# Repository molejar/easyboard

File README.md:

# Rapid Development Platform

EasyBoard Nano (EBN) represent the hardware modular concept for rapid development and prototyping.
Thanks to high scalability it's covering a wide area of applications and technologies.

## EBN HW

## EBN SW

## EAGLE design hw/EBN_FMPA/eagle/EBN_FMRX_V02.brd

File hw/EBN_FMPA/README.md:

# EBN: FM Radio Shield

#### General Info

* **Base On:** RDA5807M (Single-Chip Broadcast FM Radio Tuner with RDS)
* **Output PA:** PAM8403/PAM8406 (FilterLess 3W/5W Class-D Stereo Audio Amplifier)
* **Control Pins:** Two GPIOs for Enable/Disable MUTE and SHUTDOWN
* **Main Interface:** I2C for tuning and controlling RDA5807M

### Blocking Diagram

### PinOut

#### Connection with Core Shield

| EBN-FMPA        | EBN-KL27Z4  |
| --------------- | ----------- |
| I2C-SDA         | PTB1        |
| I2C-SCL         | PTB0        |
| SHDN            | PTA1        |
| MUTE            | PTA2        |
| AIO             | PTE30       |

### Design files

 * [Schematic & PCB (Eagle 7.x)](eagle)

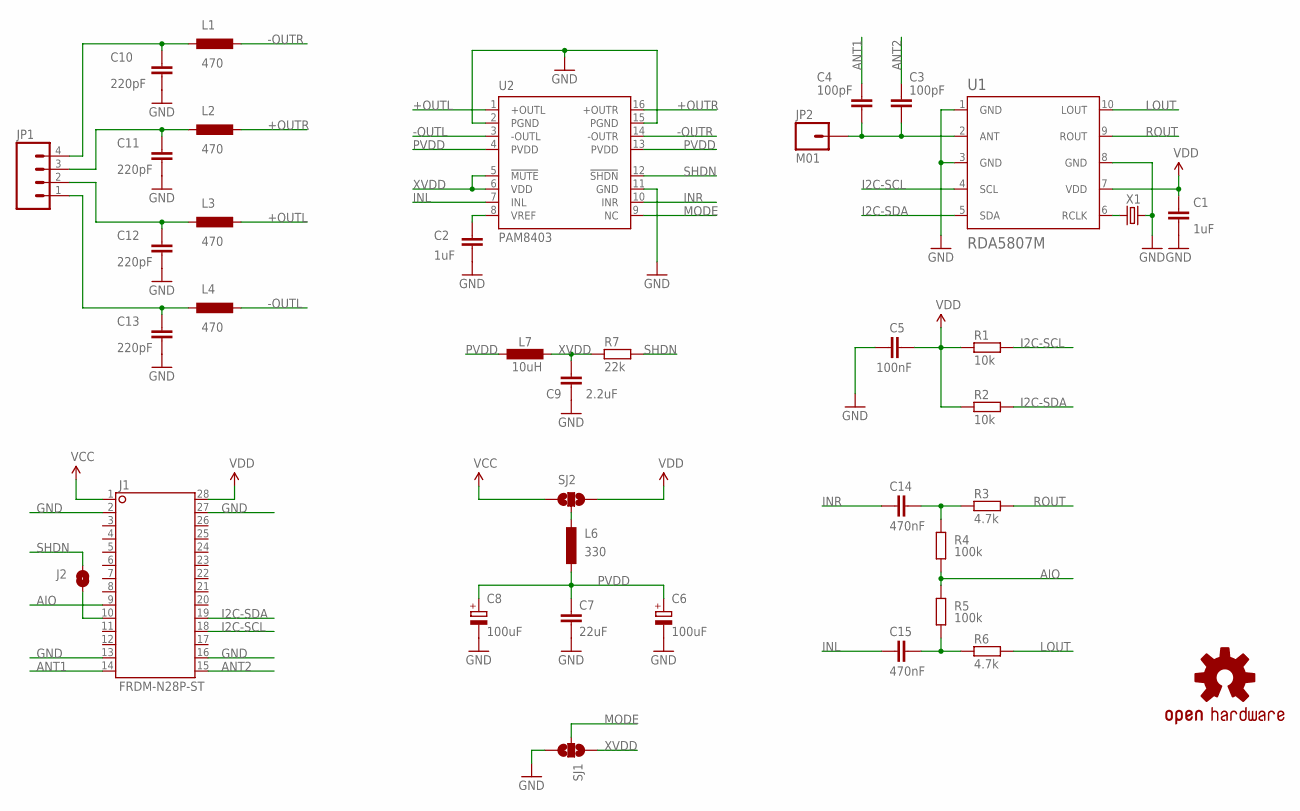
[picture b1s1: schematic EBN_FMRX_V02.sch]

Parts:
C1, C2: 1uF; C0603
C3, C4: 100pF; C0603
C5: 100nF; C0603
C6, C8: 100uF; SMC_C
C7: 22uF; C1206
C9: 2.2uF; C0603
C10, C11, C12, C13: 220pF; C0603
C14, C15: 470nF; C0603
J1: FRDM-N28P-ST; FRDM-N28P-SHIELD
J2: SJ-S; JUMPER-SMD-S1X
JP1: M04SMD_1.25MM; 1X04-1.25MM_SMD
JP2: M01; 1X01-EXTRA
L1, L2, L3, L4: 470; L0805
L6: 330; L0805
L7: 10uH; L0805
LOGO1: OSHW-LOGOS; OSHW-LOGO-S
R1, R2: 10k; R0603
R3, R6: 4.7k; R0603
R4, R5: 100k; R0603
R7: 22k; R0603
SJ1, SJ2: SJ2W-S; JUMPER-SMD-S2X
U1: RDA5807M; MSOP10
U2: PAM8403; SO16
X1: XTAL1-SMD-2P-3.2X1.5MM; SMD-2X-3215

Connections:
+OUTL: L3.2, U2.1 (+OUTL)
+OUTR: L2.2, U2.16 (+OUTR)
-OUTL: L4.2, U2.3 (-OUTL)
-OUTR: L1.2, U2.14 (-OUTR)
AIO: J1.9, R4.2, R5.2
ANT1: C4.1, J1.14
ANT2: C3.1, J1.15
GND: C1.1, C2.2, C5.2, C6.-, C7.1, C8.-, C9.1, C10.1, C11.1, C12.1, C13.1, J1.2, J1.13, J1.16, J1.27, SJ1.3, U1.1 (GND), U1.3 (GND), U1.8 (GND), U2.2 (PGND), U2.11 (GND), U2.15 (PGND), X1.2
I2C-SCL: J1.18, R1.2, U1.4 (SCL)
I2C-SDA: J1.19, R2.2, U1.5 (SDA)
INL: C15.2, U2.7 (INL)
INR: C14.2, U2.10 (INR)
LOUT: R6.2, U1.10 (LOUT)
MODE: SJ1.2, U2.9 (NC)
unnamed: C2.1, U2.8 (VREF)
unnamed: C10.2, JP1.4, L1.1
unnamed: C3.2, C4.2, JP2.P$1, U1.2 (ANT)
unnamed: C11.2, JP1.3, L2.1
unnamed: C12.2, JP1.2, L3.1
unnamed: U1.6 (RCLK), X1.1
unnamed: J1.10, J2.1
unnamed: C13.2, JP1.1, L4.1
unnamed: L6.2, SJ2.2
unnamed: C14.1, R3.1, R4.1
unnamed: C15.1, R5.1, R6.1
PVDD: C6.+, C7.2, C8.+, L6.1, L7.1, U2.4 (PVDD), U2.13 (PVDD)
ROUT: R3.2, U1.9 (ROUT)
SHDN: J2.2, R7.2, U2.12 (!SHDN)
VCC: J1.1, SJ2.1
VDD: C1.2, C5.1, J1.28, R1.1, R2.1, SJ2.3, U1.7 (VDD)
XVDD: C9.2, L7.2, R7.1, SJ1.1, U2.5 (!MUTE), U2.6 (VDD)

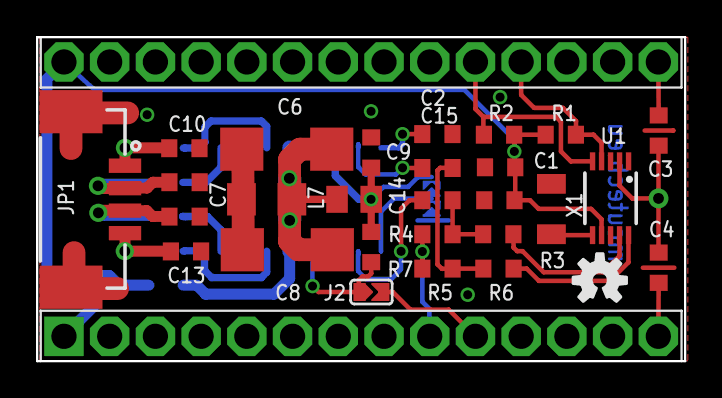
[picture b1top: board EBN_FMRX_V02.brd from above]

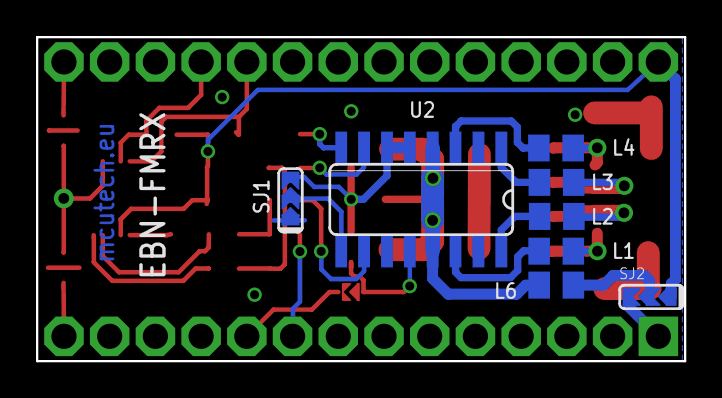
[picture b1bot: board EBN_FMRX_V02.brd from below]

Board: 2 copper layers, 36.0 x 18.0 mm, 38 parts (8 on the bottom side), 31 nets.

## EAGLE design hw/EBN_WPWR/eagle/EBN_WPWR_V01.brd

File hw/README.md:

# EasyBoard Nano HW

* [EBN_KL27Z4](EBN_KL27Z4) - KL27Z4 Core Shield
* [EBN_FMPA](EBN_FMPA) - FM Radio + 2x5W PA Shield
* [EBN_OLED](EBN_OLED) - I2C and SPI OLED Shield
* [EBN_S12D](EBN_S12D) - 12 Dimension Sensor Shield
* [EBN_WPWR](EBN_WPWR) - Wireless Power Shield
* [EBN_SBAT](EBN_SBAT) - Smart Battery Shield
* [EBN_STOR](EBN_STOR) - Storage Shield
* [EBN_GPS](EBN_GPS) - GPS + SD Card Shield
* [EBN_DUAL](EBN_DUAL) - Extendable Shield
* [EBN_PROTO](EBN_PROTO) - Prototype Shield

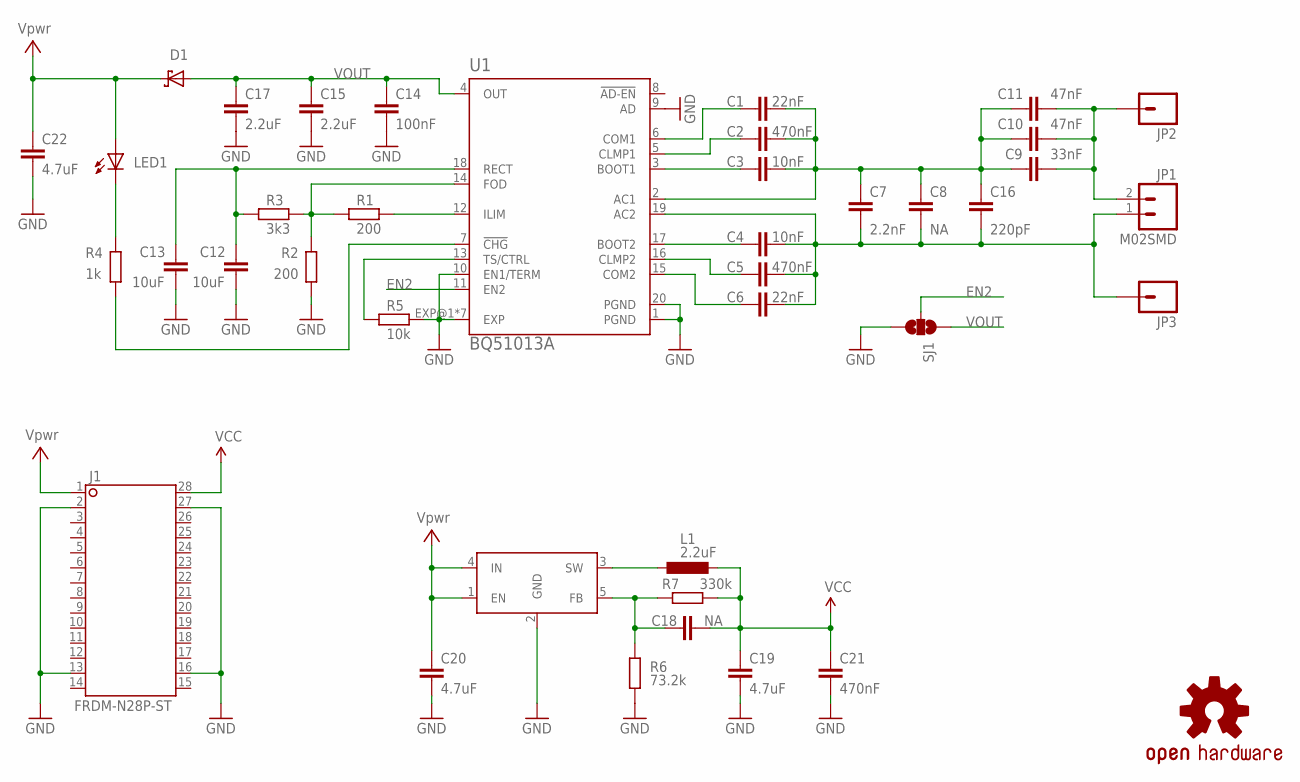
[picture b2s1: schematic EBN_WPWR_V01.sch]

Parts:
C1, C6: 22nF; C0603
C2, C5, C21: 470nF; C0603
C3, C4: 10nF; C0603
C7: 2.2nF; C0603
C8, C18: NA; C0603
C9: 33nF; C0603
C10, C11: 47nF; C0603
C12, C13: 10uF; C0805
C14: 100nF; C0603
C15, C17: 2.2uF; C0603
C16: 220pF; C0603
C19, C20, C22: 4.7uF; C0603
D1: PMEG2010BER-SHOTTKY-SOD123FL; SOD-123FL
J1: FRDM-N28P-ST; FRDM-N28P-SHIELD
JP1: M02SMD; 1X02-1.25MM_SMD
JP2, JP3: M01PTH_LONGPAD; 1X01_LONGPAD
L1: 2.2uF; LPS3015
LED1: LEDCHIPLED_0603; CHIPLED_0603
LOGO1: OSHW-LOGOS; OSHW-LOGO-S
R1, R2: 200; R0603
R3: 3k3; R0603
R4: 1k; R0603
R5: 10k; R0603
R6: 73.2k; R0603
R7: 330k; R0603
SJ1: SJ2W-S; JUMPER-SMD-S2X
U1: BQ51013A; RHL_R-VQFN-N20
U$1: MP215P; SOT23-5L

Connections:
EN2: SJ1.2, U1.11 (EN2)
GND: C12.1, C13.1, C14.1, C15.1, C17.1, C19.1, C20.1, C21.1, C22.1, J1.2, J1.13, J1.16, J1.27, R2.1, R5.2, R6.1, SJ1.3, U1.1 (PGND), U1.9 (AD), U1.10 (EN1/TERM), U1.20 (PGND), U1.EXP@1 (EXP), U1.EXP@2 (EXP), U1.EXP@3 (EXP), U1.EXP@4 (EXP), U1.EXP@5 (EXP), U1.EXP@6 (EXP), U1.EXP@7 (EXP), U$1.2 (GND)
unnamed: C3.1, U1.3 (BOOT1)
unnamed: C2.1, U1.5 (CLMP1)
unnamed: C1.1, U1.6 (COM1)
unnamed: C1.2, C2.2, C3.2, C7.2, C8.2, C9.2, C10.2, C11.2, C16.2, U1.2 (AC1)
unnamed: C4.2, C5.2, C6.2, C7.1, C8.1, C16.1, JP1.1, JP3.1, U1.19 (AC2)
unnamed: C4.1, U1.17 (BOOT2)
unnamed: C5.1, U1.16 (CLMP2)
unnamed: C6.1, U1.15 (COM2)
unnamed: C9.1, C10.1, C11.1, JP1.2, JP2.1
unnamed: LED1.C, R4.2
unnamed: R4.1, U1.7 (!CHG)
unnamed: R1.2, U1.12 (ILIM)
unnamed: R1.1, R2.2, R3.1, U1.14 (FOD)
unnamed: C12.2, C13.2, R3.2, U1.18 (RECT)
unnamed: L1.P$1 (1), U$1.3 (SW)
unnamed: C18.2, R6.2, R7.2, U$1.5 (FB)
PWR: C20.2, C22.2, D1.C, J1.1, LED1.A, U$1.1 (EN), U$1.4 (IN)
TS: R5.1, U1.13 (TS/CTRL)
VCC: C18.1, C19.2, C21.2, J1.28, L1.P$2 (2), R7.1
VOUT: C14.2, C15.2, C17.2, D1.A, SJ1.1, U1.4 (OUT)

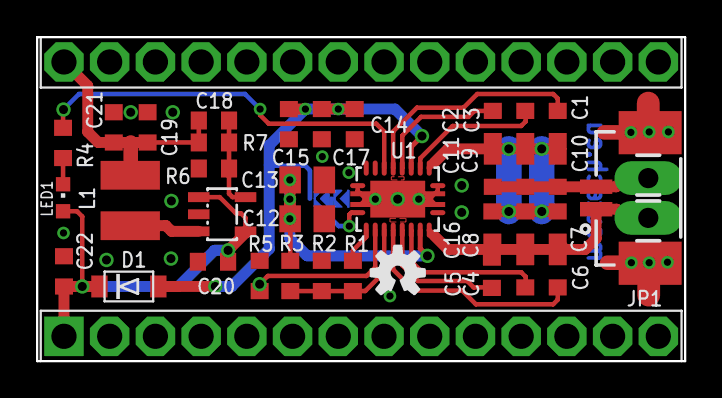
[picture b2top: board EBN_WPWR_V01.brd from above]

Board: 2 copper layers, 36.0 x 18.0 mm, 40 parts (1 on the bottom side), 22 nets.

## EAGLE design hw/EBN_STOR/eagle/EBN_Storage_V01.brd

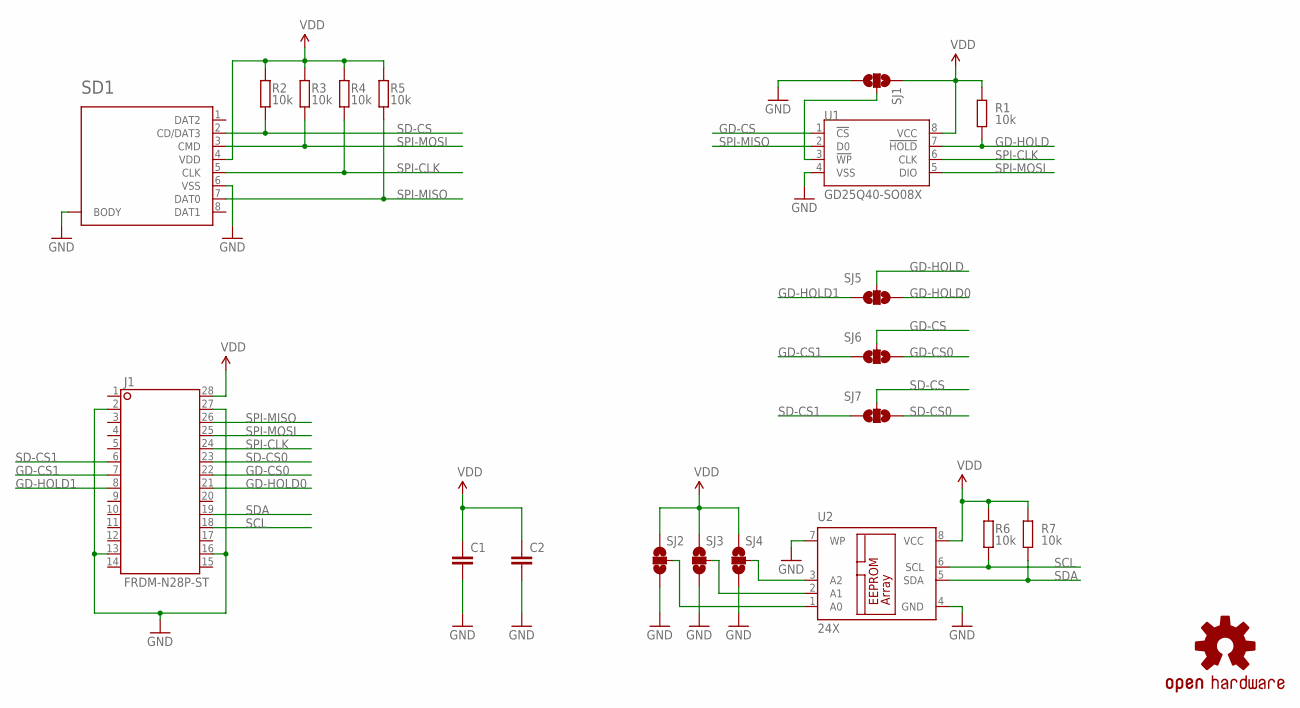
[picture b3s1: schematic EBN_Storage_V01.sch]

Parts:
C1: C-EUC0402; C0402
C2: C-EUC0603; C0603
J1: FRDM-N28P-ST; FRDM-N28P-SHIELD
LOGO1: OSHW-LOGOM; OSHW-LOGO-M
R1, R6, R7: 10k; R0603
R2, R3, R4, R5: 10k; R0402
SD1: SDCARD; MICRO-SD-01
SJ1, SJ2, SJ3, SJ4, SJ5, SJ6, SJ7: SJ2W-S; JUMPER-SMD-S2X
U1: GD25Q40-SO08X; SO08X@1
U2: 24X; SO08X

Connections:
GD-CS: SJ6.2, U1.1 (!CS)
GD-CS0: J1.22, SJ6.1
GD-CS1: J1.7, SJ6.3
GD-HOLD: R1.1, SJ5.2, U1.7 (!HOLD)
GD-HOLD0: J1.21, SJ5.1
GD-HOLD1: J1.8, SJ5.3
GND: C1.2, C2.2, J1.2, J1.13, J1.16, J1.27, SD1.6 (VSS), SD1.SHELD@0 (BODY), SD1.SHELD@1 (BODY), SJ1.1, SJ2.1, SJ3.1, SJ4.1, U1.4 (VSS), U2.4 (GND), U2.7 (WP)
unnamed: SJ4.2, U2.3 (A2)
unnamed: SJ1.2, U1.3 (!WP)
unnamed: SJ3.2, U2.2 (A1)
unnamed: SJ2.2, U2.1 (A0)
SCL: J1.18, R6.1, U2.6 (SCL)
SD-CS: R2.1, SD1.2 (CD/DAT3), SJ7.2
SD-CS0: J1.23, SJ7.1
SD-CS1: J1.6, SJ7.3
SDA: J1.19, R7.1, U2.5 (SDA)
SPI-CLK: J1.24, R4.1, SD1.5 (CLK), U1.6 (CLK)
SPI-MISO: J1.26, R5.1, SD1.7 (DAT0), U1.2 (D0)
SPI-MOSI: J1.25, R3.1, SD1.3 (CMD), U1.5 (DIO)
VDD: C1.1, C2.1, J1.28, R1.2, R2.2, R3.2, R4.2, R5.2, R6.2, R7.2, SD1.4 (VDD), SJ1.3, SJ2.3, SJ3.3, SJ4.3, U1.8 (VCC), U2.8 (VCC)

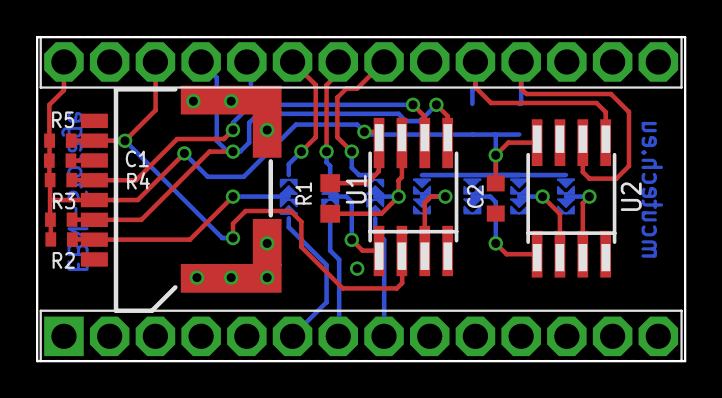
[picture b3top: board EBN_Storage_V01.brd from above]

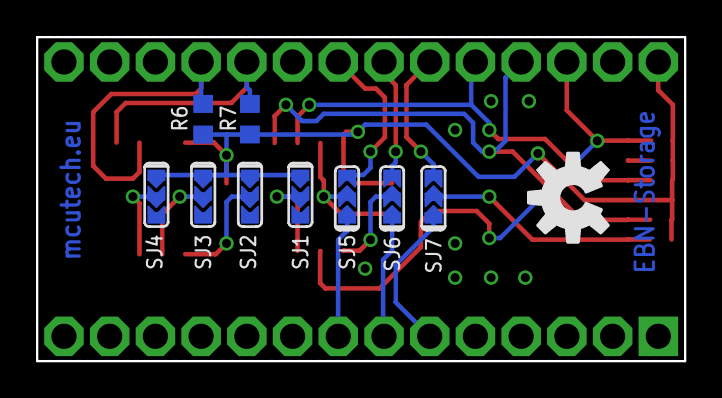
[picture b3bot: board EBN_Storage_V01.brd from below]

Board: 2 copper layers, 36.0 x 18.0 mm, 21 parts (10 on the bottom side), 20 nets.

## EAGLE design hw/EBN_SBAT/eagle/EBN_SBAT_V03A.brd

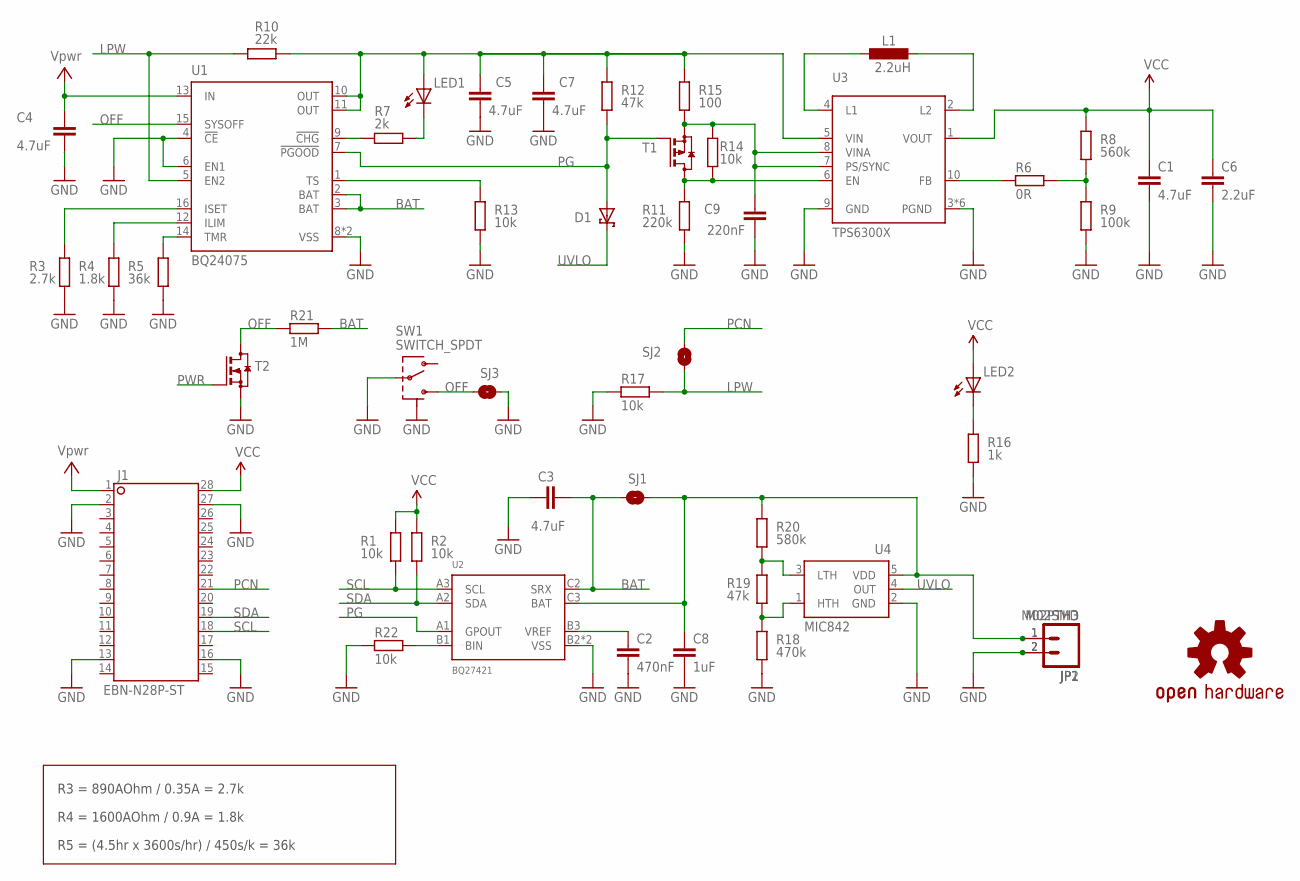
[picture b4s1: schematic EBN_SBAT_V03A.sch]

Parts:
C1, C4, C5, C7: 4.7uF; C0603
C2: 470nF; C0402
C3: 4.7uF; C0805
C6: 2.2uF; C0603
C8: 1uF; C0402
C9: 220nF; C0402
D1: -SHOTTKY-SOD323_ST; SOD323_ST
J1: EBN-N28P-ST; EBN-N28P-SHIELD
JP1: M02SMD; 1X02-1.25MM_SMD
JP2: M02PTH3; 1X02_LONGPADS
L1: 2.2uH; LPS3015
LED1, LED2: LEDCHIPLED_0603; CHIPLED_0603
LOGO1: OSHW-LOGOS; OSHW-LOGO-S
R1, R2, R13, R14, R17, R22: 10k; R0402
R3: 2.7k; R0402
R4: 1.8k; R0402
R5: 36k; R0402
R6: 0R; R0402
R7: 2k; R0402
R8: 560k; R0402
R9: 100k; R0402
R10: 22k; R0402
R11: 220k; R0402
R12, R19: 47k; R0402
R15: 100; R0402
R16: 1k; R0402
R18: 470k; R0402
R20: 580k; R0402
R21: 1M; R0402
SJ1, SJ2, SJ3: SJ-S; JUMPER-SMD-S1X
SW1: SWITCH_SPDT; SWITCH-SPST-SMD-A
T1: -PMOS-SOT323; SOT323
T2: -NMOS-SOT323; SOT323
U1: BQ24075; QFN16-3X3MM
U2: BQ27421; XBGA9
U3: TPS6300X; QFN-10_PAD
U4: MIC842; SC70

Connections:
BAT: C3.1, R21.1, SJ1.2, U1.2 (BAT), U1.3 (BAT), U2.C2 (SRX)
BATX: C8.2, JP1.1, JP2.1, R20.1, SJ1.1, U2.C3 (BAT), U4.5 (VDD)
GND: C1.2, C2.1, C3.2, C4.2, C5.2, C6.2, C7.2, C8.1, C9.2, J1.2, J1.13, J1.16, J1.27, JP1.2, JP2.2, R3.1, R4.1, R5.1, R9.1, R11.1, R13.1, R16.1, R17.2, R18.1, R22.2, SJ3.2, SW1.2, SW1.GND1 (SH), SW1.GND2 (SH), SW1.GND3 (SH), SW1.GND4 (SH), T2.2 (S), U1.4 (!CE), U1.6 (EN1), U1.8 (VSS), U1.EXT (VSS), U2.B2 (VSS), U2.C1 (VSS), U3.3 (PGND), U3.9 (GND), U3.11 (PGND), U3.12 (PGND), U3.13 (PGND), U3.14 (PGND), U3.15 (PGND), U4.2 (GND)
LPW: R10.2, R17.1, SJ2.1, U1.5 (EN2)
unnamed: L1.P$1 (1), U3.4 (L1)
unnamed: L1.P$2 (2), U3.2 (L2)
unnamed: LED2.C, R16.2
unnamed: C2.2, U2.B3 (VREF)
unnamed: R5.2, U1.14 (TMR)
unnamed: R4.2, U1.12 (ILIM)
unnamed: R18.2, R19.1, U4.1 (HTH)
unnamed: R19.2, R20.2, U4.3 (LTH)
unnamed: C9.1, R14.2, R15.1, T1.2 (S), U3.7 (PS/SYNC), U3.8 (VINA)
unnamed: R22.1, U2.B1 (BIN)
unnamed: R3.2, U1.16 (ISET)
unnamed: C5.1, C7.1, LED1.A, R10.1, R12.2, R15.2, U1.10 (OUT), U1.11 (OUT), U3.5 (VIN)
unnamed: LED1.C, R7.1
unnamed: R7.2, U1.9 (!CHG)
unnamed: R11.2, R14.1, T1.3 (D), U3.6 (EN)
unnamed: R6.1, R8.1, R9.2
unnamed: R6.2, U3.10 (FB)
OFF: R21.2, SJ3.1, SW1.3 (S), T2.3 (D), U1.15 (SYSOFF)
PCN: J1.21, SJ2.2
PG: D1.A, R12.1, T1.1 (G), U1.7 (!PGOOD), U2.A1 (GPOUT)
PWR: C4.1, J1.1, T2.1 (G), U1.13 (IN)
SCL: J1.18, R1.1, U2.A3 (SCL)
SDA: J1.19, R2.1, U2.A2 (SDA)
TS: R13.2, U1.1 (TS)
UVLO: D1.C, U4.4 (OUT)
VCC: C1.1, C6.1, J1.28, LED2.A, R1.2, R2.2, R8.2, U3.1 (VOUT)

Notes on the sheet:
R3 = 890AOhm / 0.35A = 2.7k
R4 = 1600AOhm / 0.9A = 1.8k
R5 = (4.5hr x 3600s/hr) / 450s/k = 36k

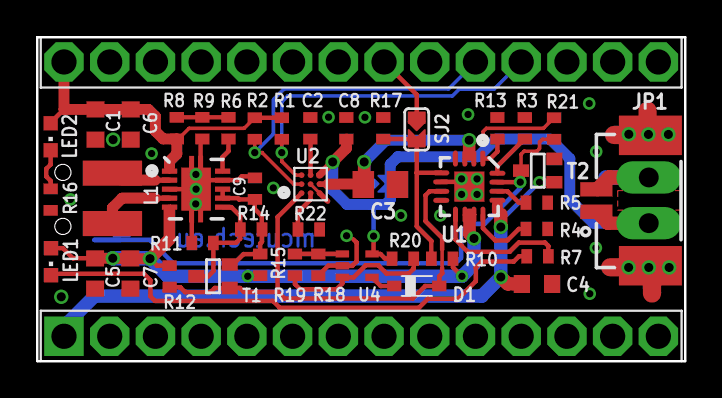
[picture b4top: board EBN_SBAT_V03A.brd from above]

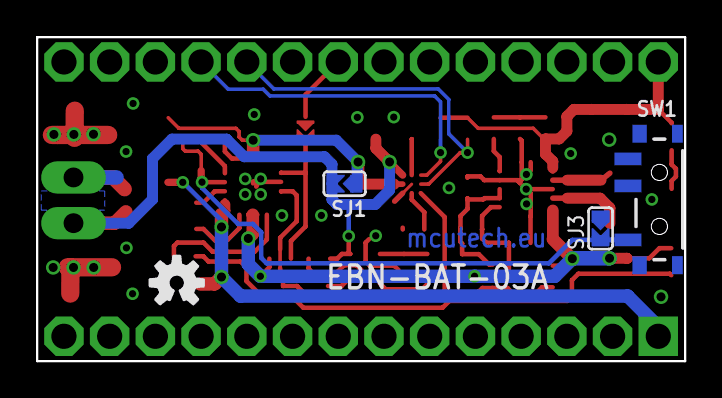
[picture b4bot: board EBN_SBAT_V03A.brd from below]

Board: 2 copper layers, 36.0 x 18.0 mm, 49 parts (4 on the bottom side), 30 nets.

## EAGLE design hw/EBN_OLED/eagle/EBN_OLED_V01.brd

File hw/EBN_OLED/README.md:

# EBN: OLED Shield

#### General Info

* **Base On:** 128x32 pixels OLED Display
* **Other:** Button and Speaker

### Blocking Diagram

### PinOut

#### Connection with Core Shield

| EBN-OLED-I2C    | EBN-KL27Z4  |
| --------------- | ----------- |
| BUTTON          | PTA4        |
| SPKR            | PTC1        |
| I2C-SDA         | PTB1        |
| I2C-SCL         | PTB0        |
| OLED-RST        | PTE0        |

| EBN-OLED-SPI    | EBN-KL27Z4  |
| --------------- | ----------- |
| BUTTON          | PTA4        |
| SPKR            | PTC1        |
| SPI-MISO        | PTC7        |
| SPI-MOSI        | PTC6        |
| SPI-SCKL        | PTC5        |
| OLED-DC         | PTC2        |
| OLED-RST        | PTE0        |

### Design files

 * [Schematic & PCB (Eagle 7.x)](eagle)

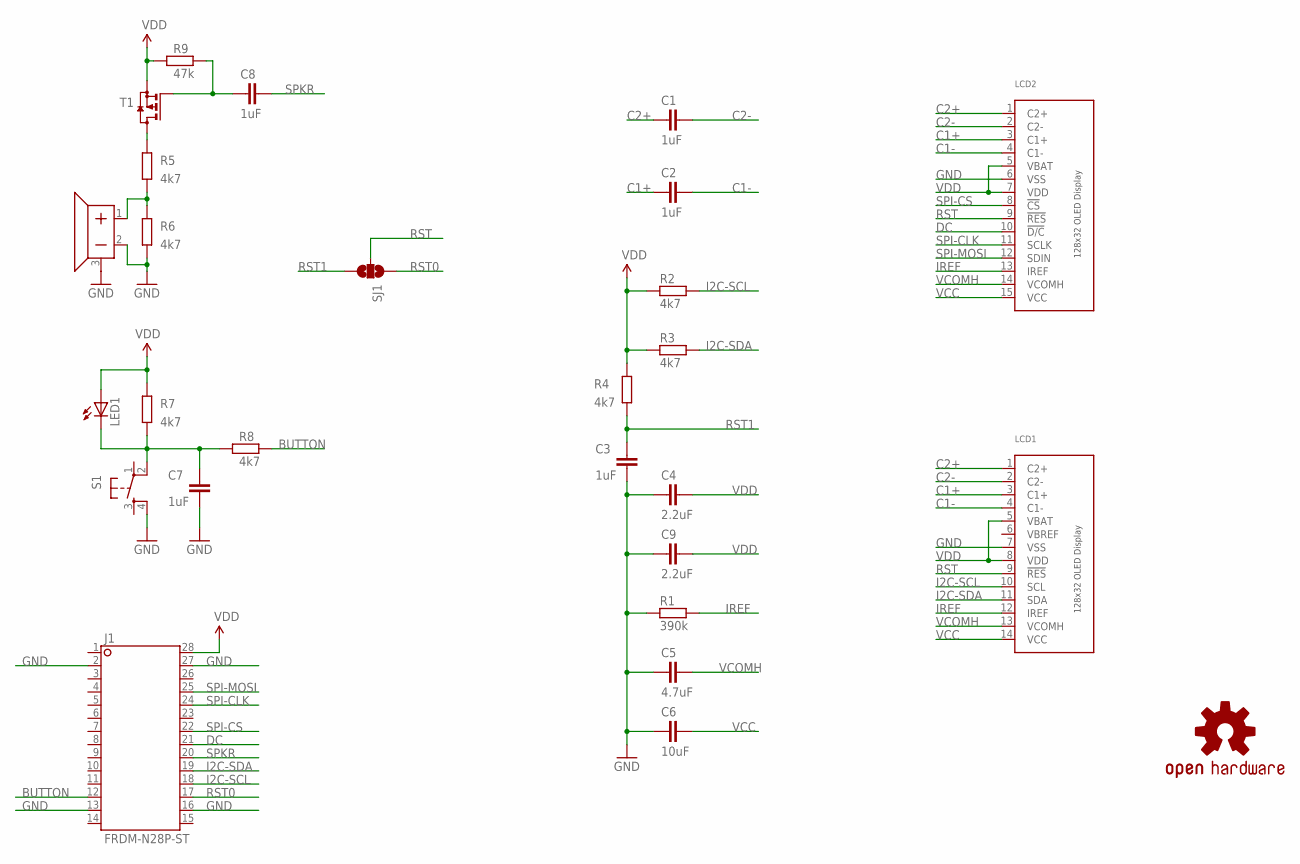
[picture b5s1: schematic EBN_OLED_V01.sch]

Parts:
C1, C2, C3, C7, C8: 1uF; C0603
C4, C9: 2.2uF; C0603
C5: 4.7uF; C0603
C6: 10uF; C0603
J1: FRDM-N28P-ST; FRDM-N28P-SHIELD
LCD1: DISP_OLED_UG-2832HSWEG02; UG-2832HSWEG02_WRAPUNDER
LCD2: DISP_OLED_UG-2832HSWEG04WRAPAROUND; UG-2832HSWEG04_WRAPAROUND
LED1: LEDCHIPLED_0805; CHIPLED_0805
LOGO1: OSHW-LOGOS; OSHW-LOGO-S
R1: 390k; R0603
R2, R3, R4, R5, R6, R7, R8: 4k7; R0603
R9: 47k; R0603
S1: SWITCH-TACT2; EVQ-PLX
SJ1: SJ2W-S; JUMPER-SMD-S2X
T1: -PMOS-SOT23; SOT23
U$1: SPEAKER; BUZZER-5MM

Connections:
BUTTON: J1.12, R8.1
C1+: C2.1, LCD1.3 (C1+), LCD2.3 (C1+)
C1-: C2.2, LCD1.4 (C1-), LCD2.4 (C1-)
C2+: C1.1, LCD1.1 (C2+), LCD2.1 (C2+)
C2-: C1.2, LCD1.2 (C2-), LCD2.2 (C2-)
DC: J1.21, LCD2.10 (!D/C)
GND: C3.1, C4.1, C5.1, C6.1, C7.1, C9.1, J1.2, J1.13, J1.16, J1.27, LCD1.7 (VSS), LCD2.6 (VSS), R1.1, R6.1, S1.4, U$1.2, U$1.3
I2C-SCL: J1.18, LCD1.10 (SCL), R2.2
I2C-SDA: J1.19, LCD1.11 (SDA), R3.2
IREF: LCD1.12 (IREF), LCD2.13 (IREF), R1.2
unnamed: R5.2, T1.3 (D)
unnamed: R5.1, R6.2, U$1.1
unnamed: C7.2, LED1.C, R7.1, R8.2, S1.2
unnamed: C8.1, R9.1, T1.1 (G)
RST: LCD1.9 (!RES), LCD2.9 (!RES), SJ1.2
RST0: J1.17, SJ1.1
RST1: C3.2, R4.1, SJ1.3
SPI-CLK: J1.24, LCD2.11 (SCLK)
SPI-CS: J1.22, LCD2.8 (!CS)
SPI-MOSI: J1.25, LCD2.12 (SDIN)
SPKR: C8.2, J1.20
VBREF: LCD1.6 (VBREF)
VCC: C6.2, LCD1.14 (VCC), LCD2.15 (VCC)
VCOMH: C5.2, LCD1.13 (VCOMH), LCD2.14 (VCOMH)
VDD: C4.2, C9.2, J1.28, LCD1.5 (VBAT), LCD1.8 (VDD), LCD2.5 (VBAT), LCD2.7 (VDD), LED1.A, R2.1, R3.1, R4.2, R7.2, R9.2, T1.2 (S)

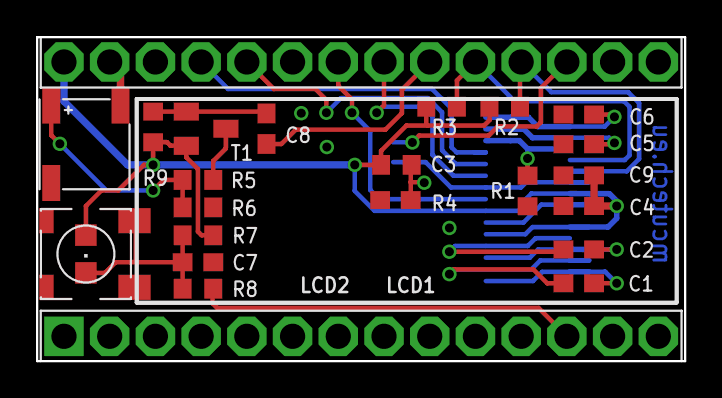
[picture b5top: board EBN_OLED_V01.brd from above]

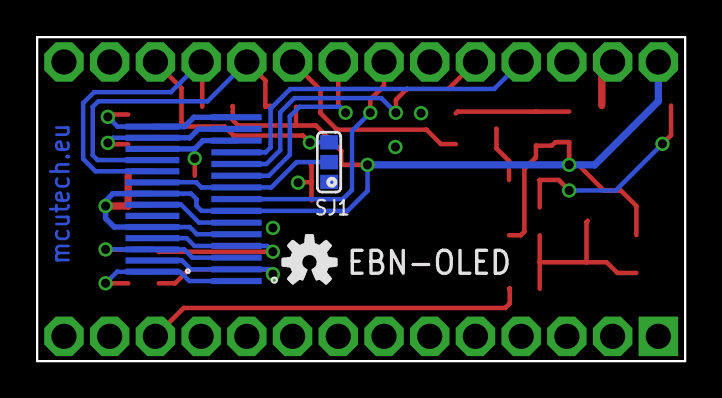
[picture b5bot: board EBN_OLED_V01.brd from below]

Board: 2 copper layers, 36.0 x 18.0 mm, 27 parts (2 on the bottom side), 24 nets.

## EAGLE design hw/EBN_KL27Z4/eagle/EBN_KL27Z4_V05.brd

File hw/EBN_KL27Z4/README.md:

# EBN: KL27Z4 Core Shield

#### General Info

* **MCU:** Freescale MKL27Z256VFM4 in QFN32 package
* **ARM Core:** Cortex-M0+, 50MHz (max)
* **Memory's:** 256kB Flash and 32kB RAM
* **Serial Interfaces:** 1xUSB-Device, 3xUART, 2xSPI, 2xI2C, 1xI2S, ...
* **Other:** 16-bit ADC, 12-bit DAC, RTC, FlexIO (4xIO-Pins)

### Blocking Diagram

### PinOut

#### Internal Connections

| Name           | Pin    | Description                |
| -------------- | ------ | -------------------------- |
| LED1 (Green)   | VCC    | Power Status LED           |
| LED2 (Red)     | PTA3   | User or Error Status LED   |
| SW1 (Button)   | PTA4   | Enter into Bootloader      |

### Design files

 * [Schematic & PCB (Eagle 7.x)](eagle)

### OSH Park

<a href="https://oshpark.com/shared_projects/JpSgUC9z"></img></a>

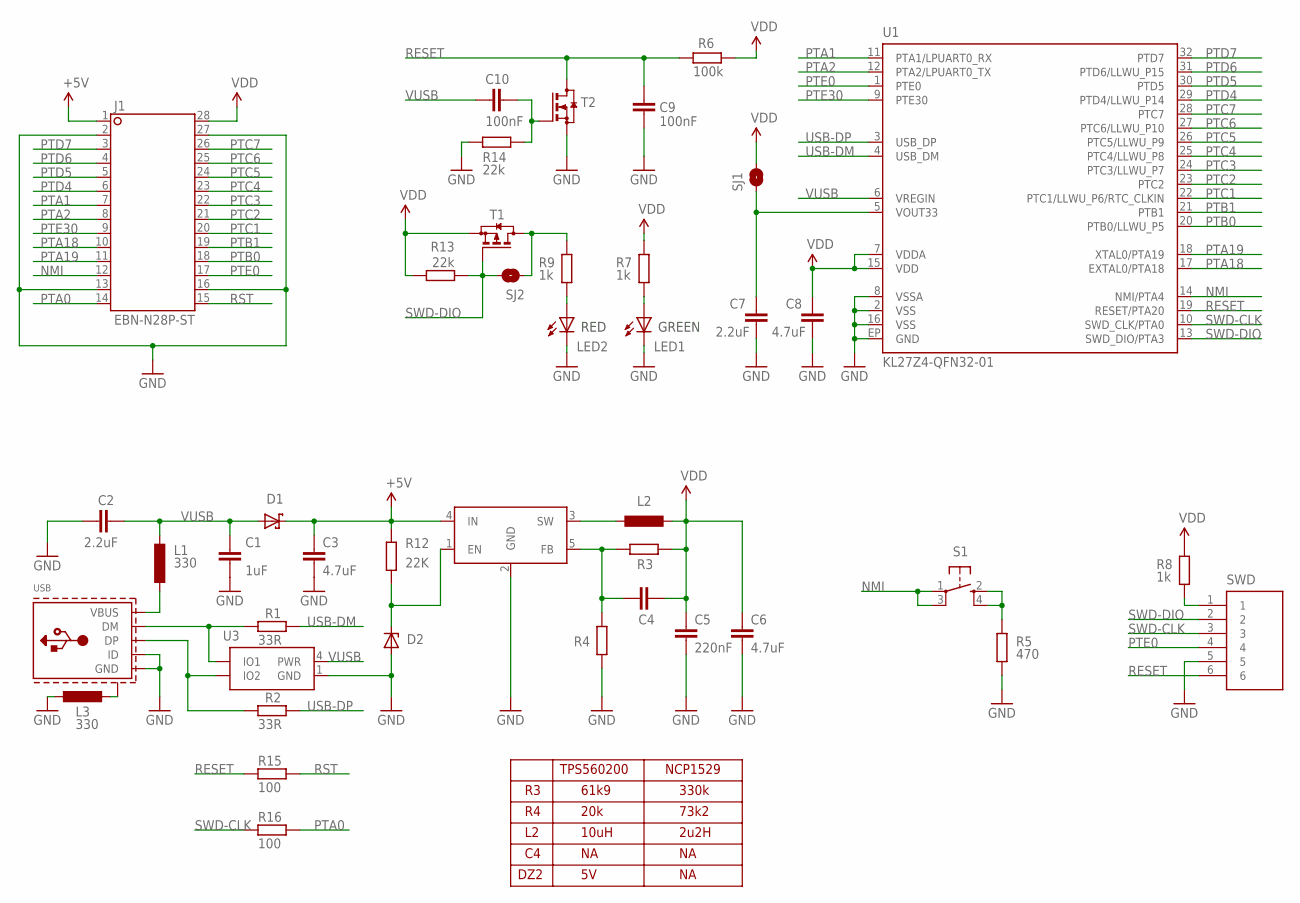
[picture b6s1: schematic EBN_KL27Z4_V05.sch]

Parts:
C1: 1uF; C0402
C2, C7: 2.2uF; C0603
C3, C6, C8: 4.7uF; C0603
C4: *; C0402
C5: 220nF; C0603
C9, C10: 100nF; C0402
D1: PMEG2010BER_SHOTTKY-SOD123FL; SOD-123FL
D2: DZ; SOD323_ST
J1: EBN-N28P-ST; EBN-N28P-SHIELD
L1, L3: 330; L0805
L2: 2u2; LPS3015
LED1, LED2: LEDCHIPLED_0603; CHIPLED_0603
R1, R2: 33R; R0402
R3, R4: *; R0402
R5: 470; R0402
R6: 100k; R0402
R7, R8, R9: 1k; R0402
R12: 22K; R0603
R13, R14: 22k; R0402
R15, R16: 100; R0402
S1: SWITCH-TACT2; KMR2
SJ1, SJ2: SJ-S; JUMPER-SMD-S1X
SWD: CON-1X6JST-SIDE; CON-JST1X6-SIDE
T1: -PMOS-SOT323; SOT323
T2: -NMOS-SOT323; SOT323
U1: KL27Z4-QFN32-01; QFN-32
U2: MP215P; SOT23-5L
U3: PRTR5V0U2X; SOT-143B
USB: USB-5P-MICRO-SMD-05; USB-MICRO-SMD-05

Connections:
+5V: C3.1, D1.C, J1.1, R12.2, U2.4 (IN)
DM: R1.1, U3.3 (IO1), USB.DM
DP: R2.1, U3.2 (IO2), USB.DP
GND: C1.1, C2.2, C3.2, C5.2, C6.2, C7.2, C8.2, C9.2, D2.A, J1.2, J1.13, J1.16, J1.27, L3.2, LED1.C, LED2.C, R4.1, R5.1, R14.1, SWD.5, T2.2 (S), U1.2 (VSS), U1.8 (VSSA), U1.16 (VSS), U1.EP (GND), U2.2 (GND), U3.1 (GND), USB.GND, USB.ID
unnamed: L1.1, USB.VBUS
unnamed: L3.1, USB.SHILD@1 (SHILD), USB.SHILD@2 (SHILD), USB.SHILD@3 (SHILD), USB.SHILD@4 (SHILD)
unnamed: LED1.A, R7.1
unnamed: D2.C, R12.1, U2.1 (EN)
unnamed: R5.2, S1.2 (3), S1.4
unnamed: C7.1, SJ1.1, U1.5 (VOUT33)
unnamed: R8.1, SWD.1
unnamed: LED2.A, R9.1
unnamed: R9.2, SJ2.1, T1.3 (D)
unnamed: C10.2, R14.2, T2.1 (G)
unnamed: L2.P$1 (1), U2.3 (SW)
unnamed: C4.1, R3.1, R4.2, U2.5 (FB)
NMI: J1.12, S1.1, S1.3 (2), U1.14 (NMI/PTA4)
PTA0: J1.14, R16.1
PTA1: J1.7, U1.11 (PTA1/LPUART0_RX)
PTA2: J1.8, U1.12 (PTA2/LPUART0_TX)
PTA18: J1.10, U1.17 (EXTAL0/PTA18)
PTA19: J1.11, U1.18 (XTAL0/PTA19)
PTB0: J1.18, U1.20 (PTB0/LLWU_P5)
PTB1: J1.19, U1.21 (PTB1)
PTC1: J1.20, U1.22 (PTC1/LLWU_P6/RTC_CLKIN)
PTC2: J1.21, U1.23 (PTC2)
PTC3: J1.22, U1.24 (PTC3/LLWU_P7)
PTC4: J1.23, U1.25 (PTC4/LLWU_P8)
PTC5: J1.24, U1.26 (PTC5/LLWU_P9)
PTC6: J1.25, U1.27 (PTC6/LLWU_P10)
PTC7: J1.26, U1.28 (PTC7)
PTD4: J1.6, U1.29 (PTD4/LLWU_P14)
PTD5: J1.5, U1.30 (PTD5)
PTD6: J1.4, U1.31 (PTD6/LLWU_P15)
PTD7: J1.3, U1.32 (PTD7)
PTE0: J1.17, SWD.4, U1.1 (PTE0)
PTE30: J1.9, U1.9 (PTE30)
RESET: C9.1, R6.2, R15.2, SWD.6, T2.3 (D), U1.19 (RESET/PTA20)
RST: J1.15, R15.1
SWD-CLK: R16.2, SWD.3, U1.10 (SWD_CLK/PTA0)
SWD-DIO: R13.1, SJ2.2, SWD.2, T1.1 (G), U1.13 (SWD_DIO/PTA3)
USB-DM: R1.2, U1.4 (USB_DM)
USB-DP: R2.2, U1.3 (USB_DP)
VDD: C4.2, C5.1, C6.1, C8.1, J1.28, L2.P$2 (2), R3.2, R6.1, R7.2, R8.2, R13.2, SJ1.2, T1.2 (S), U1.7 (VDDA), U1.15 (VDD)
VUSB: C1.2, C2.1, C10.1, D1.A, L1.2, U1.6 (VREGIN), U3.4 (PWR)

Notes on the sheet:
TPS560200
NCP1529
61k9
20k
10uH
330k
73k2
2u2H
DZ2
RED
GREEN

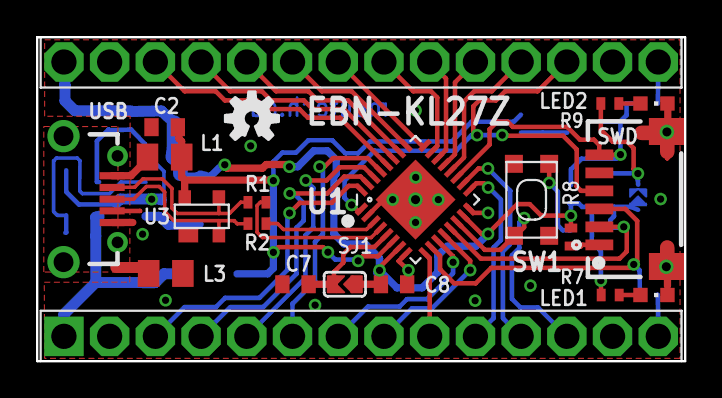
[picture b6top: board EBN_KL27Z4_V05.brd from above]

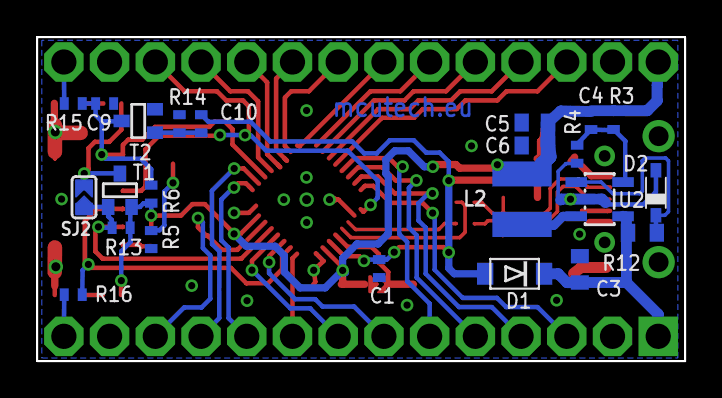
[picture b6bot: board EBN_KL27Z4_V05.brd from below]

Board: 2 copper layers, 36.0 x 18.0 mm, 43 parts (23 on the bottom side), 45 nets.

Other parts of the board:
U$2: OSHW-LOGO-S

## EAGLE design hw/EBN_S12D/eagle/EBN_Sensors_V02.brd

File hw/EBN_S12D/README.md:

# EBN: Sensor Shield

#### General Info

* **Accelerometer:** FXOS8700
* **Magnetometer:** FXOS8700
* **Barometer:** MPL3115
* **Gyroscope:** FXAS21002
* **Humidity:** SHT2X

### Block Diagram

### PinOut

#### Connection with Core Shield

| EBN-S12D        | EBN-KL27Z4  |
| --------------- | ----------- |
| I2C-SDA         | PTB1        |
| I2C-SCL         | PTB0        |
| IRQ (20 / 17)   | PTC1 / PTE0 |

### Design files

 * [Schematic & PCB (Eagle 7.x)](eagle)

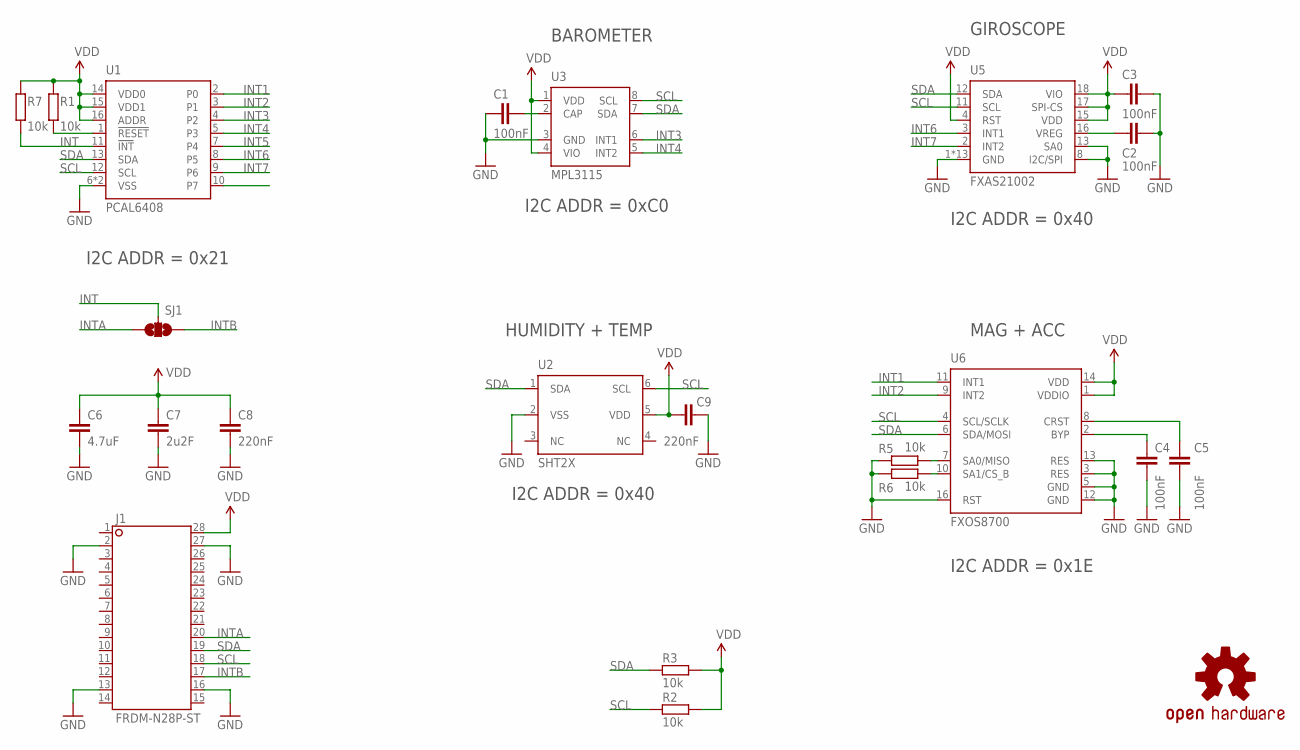
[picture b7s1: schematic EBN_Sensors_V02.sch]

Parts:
C1, C2, C3, C4, C5: 100nF; C0402
C6: 4.7uF; C0603
C7: 2u2F; C0603
C8, C9: 220nF; C0402
J1: FRDM-N28P-ST; FRDM-N28P-SHIELD
LOGO1: OSHW-LOGOS; OSHW-LOGO-S
R1, R2, R3, R5, R6, R7: 10k; R0402
SJ1: SJ2W-S; JUMPER-SMD-S2X
U1: PCAL6408; QFN16-3X3MM
U2: SHT2X; DFN6_3X3
U3: MPL3115; LGA-8
U5: FXAS21002; QFN24
U6: FXOS8700; QFN16-FX

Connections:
GND: C1.1, C2.1, C3.1, C4.2, C5.2, C6.2, C7.2, C8.2, C9.1, J1.2, J1.13, J1.16, J1.27, R5.2, R6.2, U1.6 (VSS), U1.EXT (VSS), U2.2 (VSS), U3.3 (GND), U5.1 (GND), U5.5 (GND), U5.6 (GND), U5.7 (GND), U5.8 (I2C/SPI), U5.9 (GND), U5.10 (GND), U5.13 (SA0), U5.14 (GND), U5.19 (GND), U5.20 (GND), U5.21 (GND), U5.22 (GND), U5.23 (GND), U5.24 (GND), U6.3 (RES), U6.5 (GND), U6.12 (GND), U6.13 (RES), U6.16 (RST)
INT: R7.2, SJ1.2, U1.11 (!INT)
INT1: U1.2 (P0), U6.11 (INT1)
INT2: U1.3 (P1), U6.9 (INT2)
INT3: U1.4 (P2), U3.6 (INT1)
INT4: U1.5 (P3), U3.5 (INT2)
INT5: U1.7 (P4)
INT6: U1.8 (P5), U5.3 (INT1)
INT7: U1.9 (P6), U5.2 (INT2)
INTA: J1.20, SJ1.3
INTB: J1.17, SJ1.1
unnamed: R5.1, U6.7 (SA0/MISO)
unnamed: R6.1, U6.10 (SA1/CS_B)
unnamed: C2.2, U5.16 (VREG)
unnamed: R1.2, U1.1 (!RESET)
unnamed: C1.2, U3.2 (CAP)
unnamed: C4.1, U6.2 (BYP)
unnamed: C5.1, U6.8 (CRST)
SCL: J1.18, R2.1, U1.12 (SCL), U2.6 (SCL), U3.8 (SCL), U5.11 (SCL), U6.4 (SCL/SCLK)
SDA: J1.19, R3.1, U1.13 (SDA), U2.1 (SDA), U3.7 (SDA), U5.12 (SDA), U6.6 (SDA/MOSI)
VDD: C3.2, C6.1, C7.1, C8.1, C9.2, J1.28, R1.1, R2.2, R3.2, R7.1, U1.14 (VDD0), U1.15 (VDD1), U1.16 (ADDR), U2.5 (VDD), U3.1 (VDD), U3.4 (VIO), U5.4 (RST), U5.15 (VDD), U5.17 (SPI-CS), U5.18 (VIO), U6.1 (VDDIO), U6.14 (VDD)

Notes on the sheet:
I2C ADDR = 0x21
I2C ADDR = 0x1E
I2C ADDR = 0x40
I2C ADDR = 0xC0
MAG + ACC
GIROSCOPE
BAROMETER
HUMIDITY + TEMP

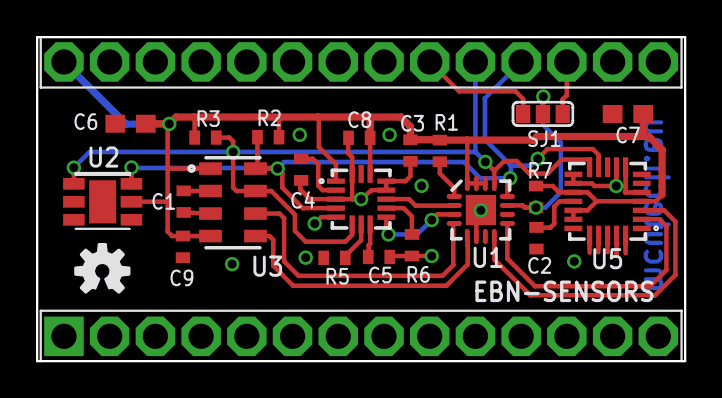
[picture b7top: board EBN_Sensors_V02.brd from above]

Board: 2 copper layers, 36.0 x 18.0 mm, 23 parts (0 on the bottom side), 20 nets.

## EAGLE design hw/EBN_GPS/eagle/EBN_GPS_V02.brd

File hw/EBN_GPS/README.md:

# EBN: GPS + SD Card Shield

#### General Info

* **Base On:** GPS module Ublox Max-7Q (also compatible with Quectel L70/L76 or SIMCom SIM26ML/SIM68M modules)
* **Optional Storage:** Micro SD Card or SPI Flash

### Block Diagram

### PinOut

#### Connection with Core Shield

| EBN-GPS         | EBN-KL27Z4  |
| --------------- | ----------- |
| SD-MISO         | PTC7        |
| SD-MOSI         | PTC6        |
| SD-SCKL         | PTC5        |
| SD-SCKL         | PTC5        |
| SD-CS (06 / 23) | PTD4 / PTC4 |
| UART-TX         | PTA1        |
| UART-RX         | PTA2        |
| RST             | PTE30       |
| PPS             | PTA18       |
| INT             | PTA4        |
| FC-ON           | PTE0        |

### Design files

 * [Schematic & PCB (Eagle 7.x)](eagle)

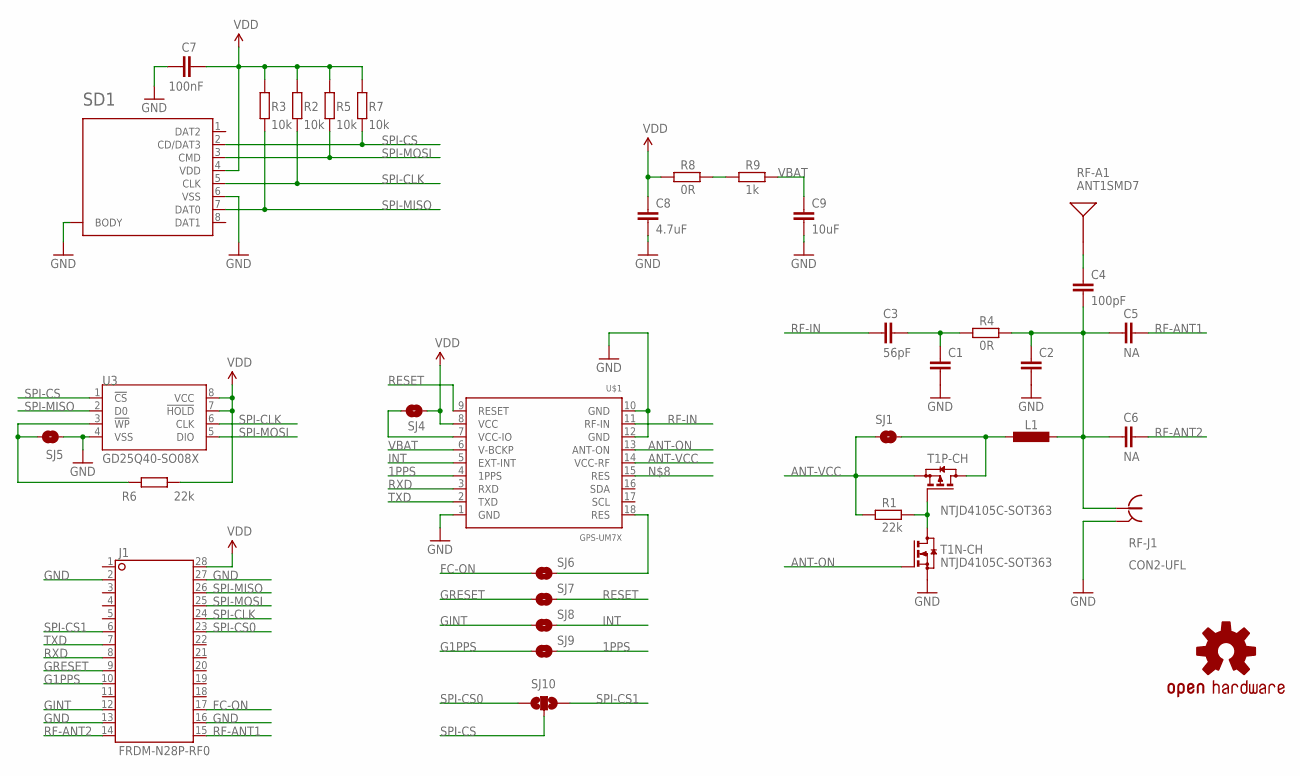
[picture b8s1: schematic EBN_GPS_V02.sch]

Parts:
C1, C2: C-EUC0402; C0402
C3: 56pF; C0402
C4: 100pF; C0402
C5, C6: NA; C0603
C7: 100nF; C0402
C8: 4.7uF; C0805
C9: 10uF; C0805
J1: FRDM-N28P-RF0; EBN-N28P-SHRF0
L1: L-EUL0603; L0603
LOGO1: OSHW-LOGOM; OSHW-LOGO-M
R1, R6: 22k; R0402
R2, R3, R5, R7: 10k; R0402
R4: 0R; R0402
R8: 0R; R0603
R9: 1k; R0603
RF-A1: ANT1SMD7; ANT-GPS0
RF-J1: CON2-UFL; RF-CON-U.FL
SD1: SDCARD00; MICRO-SD-00
SJ1, SJ4, SJ5, SJ6, SJ7, SJ8, SJ9: SJ-S; JUMPER-SMD-S1X
SJ10: SJ2W-S; JUMPER-SMD-S2X
T1: NTJD4105C-SOT363; SOT363
U3: GD25Q40-SO08X; SO08X
U$1: GPS-UM7X; GPS-XX7X

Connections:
1PPS: SJ9.2, U$1.4 (1PPS)
ANT-ON: T1.2 (G), U$1.13 (ANT-ON)
ANT-VCC: R1.2, SJ1.1, T1.4 (S), U$1.14 (VCC-RF)
FC-ON: J1.17, SJ6.1
G1PPS: J1.10, SJ9.1
GINT: J1.12, SJ8.1
GND: C1.2, C2.2, C7.2, C8.2, C9.2, J1.2, J1.13, J1.16, J1.27, RF-J1.GND@0 (GND), RF-J1.GND@1 (GND), RF-J1.GND@2 (GND), SD1.6 (VSS), SD1.SHELD@0 (BODY), SD1.SHELD@1 (BODY), SJ5.1, T1.1 (S), U3.4 (VSS), U$1.1 (GND), U$1.10 (GND), U$1.12 (GND)
GRESET: J1.9, SJ7.1
INT: SJ8.2, U$1.5 (EXT-INT)
unnamed: C4.1, RF-A1.SIG
unnamed: R8.1, R9.2
unnamed: SJ6.2, U$1.18 (RES)
unnamed: R6.2, SJ5.2, U3.3 (!WP)
unnamed: SJ4.1, U$1.7 (VCC-IO)
unnamed: R1.1, T1.5 (G), T1.6 (D)
unnamed: L1.1, SJ1.2, T1.3 (D)
unnamed: C2.1, C4.2, C5.1, C6.1, L1.2, R4.1, RF-J1.SIG
unnamed: C1.1, C3.2, R4.2
RESET: SJ7.2, U$1.9 (RESET)
RF-ANT1: C5.2, J1.15
RF-ANT2: C6.2, J1.14
RF-IN: C3.1, U$1.11 (RF-IN)
RXD: J1.8, U$1.3 (RXD)
SPI-CLK: J1.24, R2.1, SD1.5 (CLK), U3.6 (CLK)
SPI-CS: R7.1, SD1.2 (CD/DAT3), SJ10.2, U3.1 (!CS)
SPI-CS0: J1.23, SJ10.1
SPI-CS1: J1.6, SJ10.3
SPI-MISO: J1.26, R3.1, SD1.7 (DAT0), U3.2 (D0)
SPI-MOSI: J1.25, R5.1, SD1.3 (CMD), U3.5 (DIO)
TXD: J1.7, U$1.2 (TXD)
VBAT: C9.1, R9.1, U$1.6 (V-BCKP)
VDD: C7.1, C8.1, J1.28, R2.2, R3.2, R5.2, R6.1, R7.2, R8.2, SD1.4 (VDD), SJ4.2, U3.7 (!HOLD), U3.8 (VCC), U$1.8 (VCC)

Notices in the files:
parts and their libraries:
SparkFun-Aesthetics: Licensing: Creative Commons ShareAlike 4.0 International - https://creativecommons.org/licenses/by-sa/4.0
